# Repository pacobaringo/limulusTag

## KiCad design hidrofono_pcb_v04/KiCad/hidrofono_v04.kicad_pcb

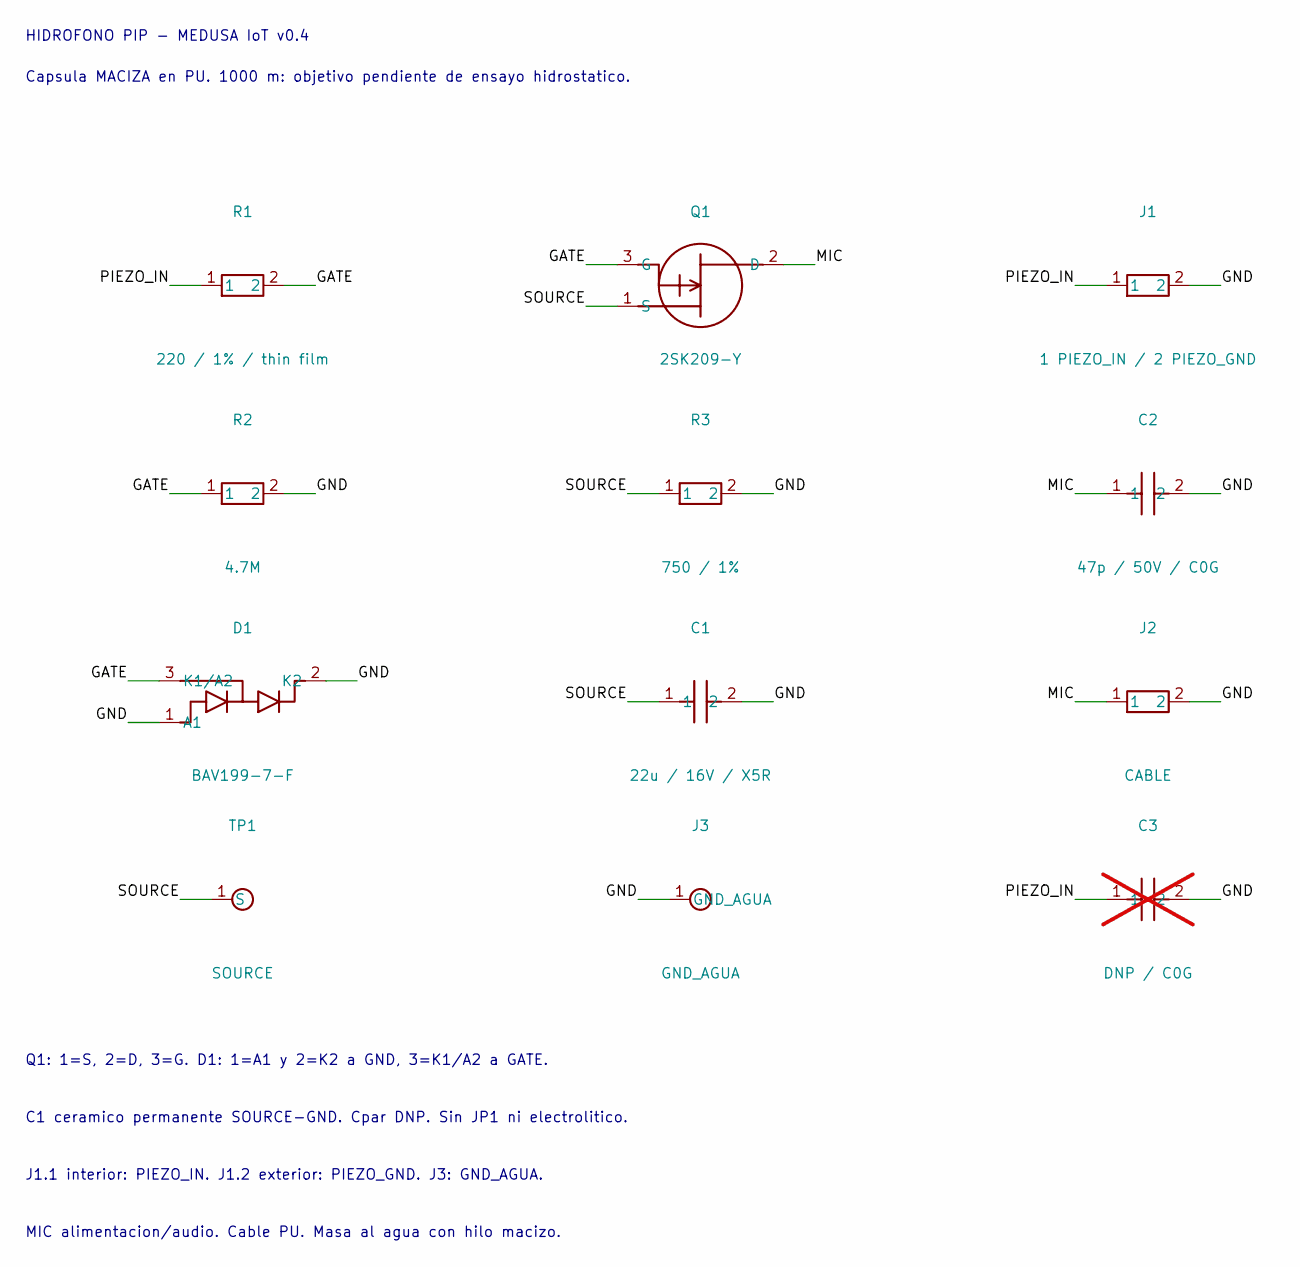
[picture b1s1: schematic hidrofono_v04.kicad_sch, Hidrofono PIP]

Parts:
C1: 22u / 16V / X5R; C1; MPN C3216X5R1C226M160AB
C2: 47p / 50V / C0G; C2; MPN C0603C470J5GACTU
C3: DNP / C0G; C3; MPN Por seleccionar tras ensayo; not fitted
D1: BAV199-7-F; D1; MPN BAV199-7-F
J1: 1 PIEZO_IN / 2 PIEZO_GND; J1
J2: CABLE; J2
J3: GND_AGUA; J3
Q1: 2SK209-Y; Q1; MPN 2SK209-Y(TE85L,F)
R1: 220 / 1% / thin film; R1; MPN RT1206FRE07220RL
R2: 4.7M; R2; MPN RC1206FR-074M7L
R3: 750 / 1%; R3; MPN RC1206FR-07750RL
TP1: SOURCE; TP1

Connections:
/GATE: D1.3 (K1/A2), Q1.3 (G), R1.2, R2.1
/GND: C1.2, C2.2, C3.2, D1.1 (A1), D1.2 (K2), J1.2, J2.2, J3.1, R2.2, R3.2
/MIC: C2.1, J2.1, Q1.2 (D)
/PIEZO_IN: C3.1, J1.1, R1.1
/SOURCE: C1.1, Q1.1 (S), R3.1, TP1.1

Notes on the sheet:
HIDROFONO PIP - MEDUSA IoT v0.4
Capsula MACIZA en PU. 1000 m: objetivo pendiente de ensayo hidrostatico.
Q1: 1=S, 2=D, 3=G. D1: 1=A1 y 2=K2 a GND, 3=K1/A2 a GATE.
C1 ceramico permanente SOURCE-GND. Cpar DNP. Sin JP1 ni electrolitico.
J1.1 interior: PIEZO_IN. J1.2 exterior: PIEZO_GND. J3: GND_AGUA.
MIC alimentacion/audio. Cable PU. Masa al agua con hilo macizo.

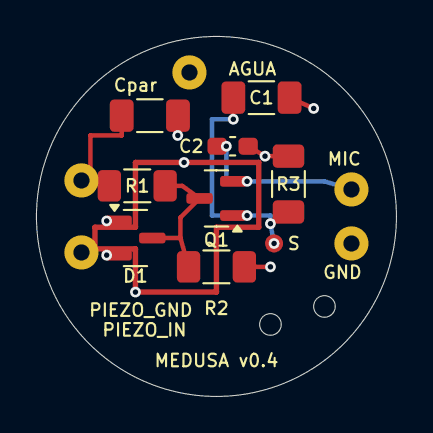
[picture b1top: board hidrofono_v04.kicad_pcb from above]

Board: 2 copper layers, 20.0 x 20.0 mm, 14 parts (0 on the bottom side), 5 nets.

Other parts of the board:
H1: strain relief; H1
H2: strain relief; H2

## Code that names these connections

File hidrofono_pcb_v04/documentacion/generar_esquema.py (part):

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    [PP('J2', '2'), (80, 27), (80, RAIL)],
    [PP('J3', '1'), (88, RAIL)],
]
LABELS = [('PIEZO_IN', (20, 36), 0), ('GATE', (43.5, 36), 0), ('MIC', (62, 25), 0),
          ('SOURCE', (61, 42), 0), ('GND', (30, RAIL), 0)]


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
